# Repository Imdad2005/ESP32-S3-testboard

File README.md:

# ESP32-S3 Testboard

A custom ESP32-S3 test and development board designed in KiCad 9 for embedded systems and IoT prototyping.
Integrates the ESP32-S3-WROOM-1 module with power regulation, onboard sensing, programming interfaces,
and peripheral expansion on a compact 50 × 50 mm PCB.

---

## Board Preview

| Top | Bottom |
|-----|--------|
|  |  |

---

## Features

- **ESP32-S3-WROOM-1** — Wi-Fi + Bluetooth module, 8 MB flash
- **USB-C** — power and programming interface with ESD protection
- **Si7021-A20** — onboard temperature and humidity sensor
- **QWIIC connector** — I2C expansion for external sensors
- **BOOT / RESET / User buttons**
- **RGB LED** and 3.3 V power indicator LED
- **2×5 SPI expansion header**
- **2×3 programming header**
- **4× mounting holes** (3.2 mm)

---

## Power

| Rail  | Source                         |
|-------|--------------------------------|
| 5 V   | USB-C                          |
| 3.3 V | LM1117MP-3.3 voltage regulator |

---

## PCB Specifications

| Parameter        | Value      |
|------------------|------------|
| EDA Tool         | KiCad 9    |
| Copper Layers    | 4          |
| Board Dimensions | 50 × 50 mm |
| Mounting Holes   | 4 × 3.2 mm |

---

## Repository Structure

```
ESP32-S3-testboard/
├── hardware/
│   ├── ESP32-S3-testboard.kicad_pro
│   ├── ESP32-S3-testboard.kicad_sch
│   └── ESP32-S3-testboard.kicad_pcb
├── fabrications/
│   ├── BOM.csv
│   └── gerbers.zip
├── docs/
│   ├── ESP32-S3-testboard.pdf
│   ├── esp32-s3-wroom-2_datasheet_en.pdf
│   ├── pcb_top.png
│   └── pcb_bottom.png
├── .gitignore
└── README.md
```

---

## Tools

- [KiCad 9](https://www.kicad.org/)

---

## Author

**Imdad Aqueel**  
B.Tech in Electronic and Communication Engineering, Bengaluru

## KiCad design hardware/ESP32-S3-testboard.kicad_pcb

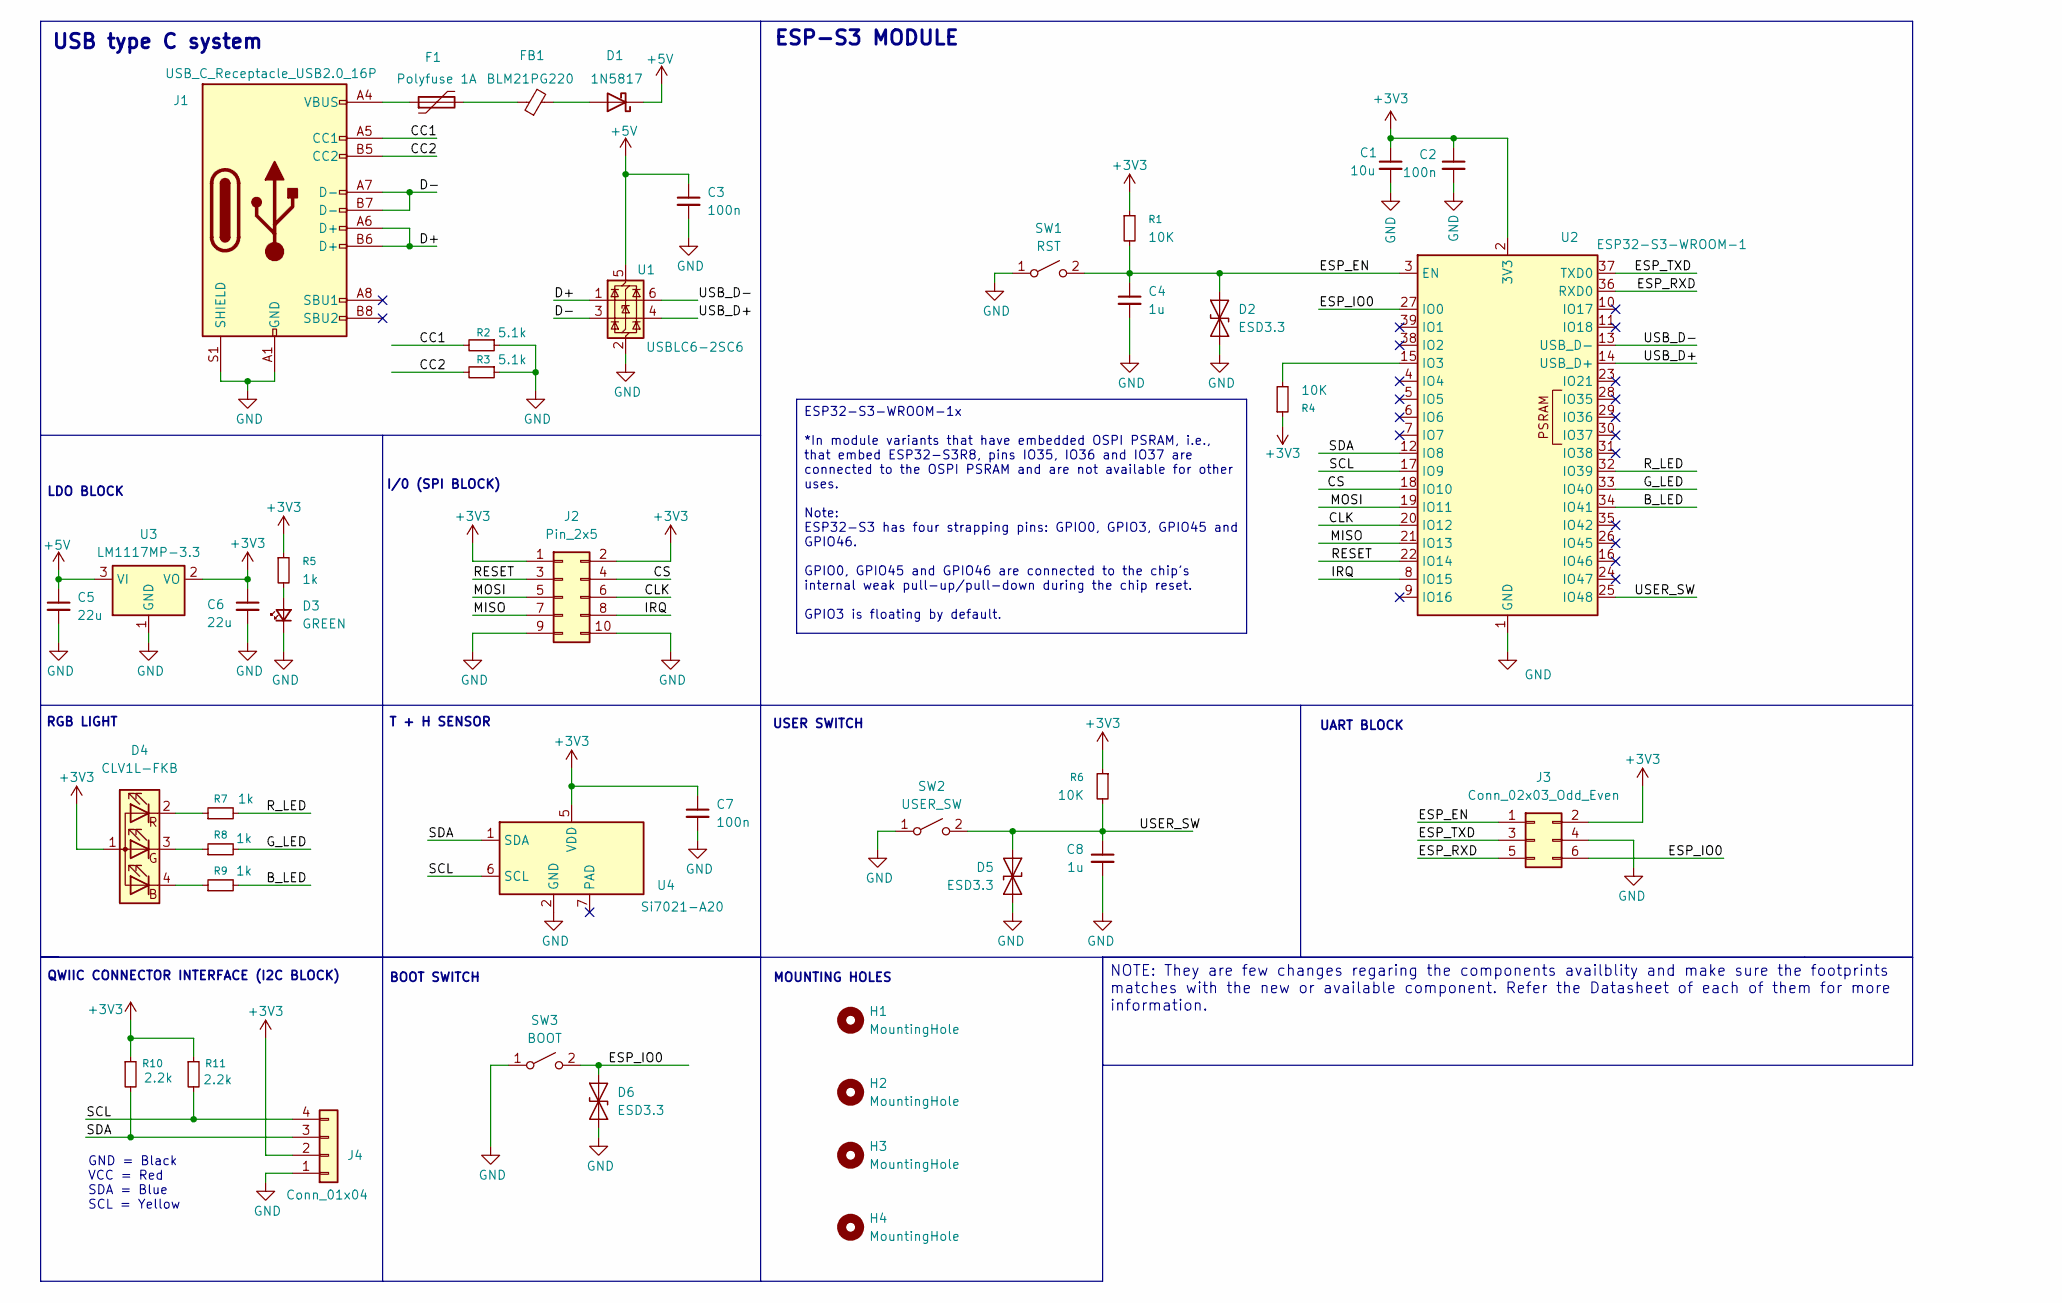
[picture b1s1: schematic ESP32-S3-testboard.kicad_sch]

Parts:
C1: 10u; C_0603_1608Metric
C2, C3, C7: 100n; C_0402_1005Metric_Pad0.74x0.62mm_HandSolder
C4, C8: 1u; C_0603_1608Metric
C5, C6: 22u; C_0805_2012Metric
D1: 1N5817; D_DO-41_SOD81_P10.16mm_Horizontal
D2, D5, D6: ESD3.3; D_SOD-923
D3: GREEN; LED_0603_1608Metric
D4: CLV1L-FKB; LED_Cree-PLCC4_3.2x2.8mm_CCW
F1: Polyfuse 1A; Fuse_1206_3216Metric
FB1: BLM21PG220; L_0805_2012Metric
H1, H2, H3, H4: MountingHole; MountingHole_3.2mm_M3
J1: USB_C_Receptacle_USB2.0_16P; USB_C_Receptacle_GCT_USB4105-xx-A_16P_TopMnt_Horizontal
J2: Pin_2x5; PinHeader_2x05_P2.54mm_Vertical
J3: Conn_02x03_Odd_Even; PinHeader_2x03_P2.54mm_Vertical
J4: Conn_01x04; JST_SH_SM04B-SRSS-TB_1x04-1MP_P1.00mm_Horizontal
R1, R4, R6: 10K; R_0402_1005Metric_Pad0.72x0.64mm_HandSolder
R2, R3: 5.1k; R_0402_1005Metric_Pad0.72x0.64mm_HandSolder
R5, R7, R8, R9: 1k; R_0402_1005Metric_Pad0.72x0.64mm_HandSolder
R10, R11: 2.2k; R_0402_1005Metric_Pad0.72x0.64mm_HandSolder
SW1: RST; SW_SPST_B3U-1000P
SW2: USER_SW; SW_Tactile_SPST_Angled_PTS645Vx31-2LFS
SW3: BOOT; SW_SPST_B3U-1000P
U1: USBLC6-2SC6; SOT-23-6
U2: ESP32-S3-WROOM-1
U3: LM1117MP-3.3; SOT-223-3_TabPin2
U4: Si7021-A20; DFN-6-1EP_3x3mm_P1mm_EP1.5x2.4mm

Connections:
+3V3: C1.1, C2.1, C6.1, C7.1, D4.1 (A), J2.1, J2.2, J3.2, J4.2, R1.1, R4.1, R5.1, R6.1, R10.1, R11.1, U2.2 (3V3), U3.2 (VO), U4.5 (VDD)
+5V: C3.1, C5.1, D1.1 (K), U1.5 (VBUS), U3.3 (VI)
/B_LED: R9.2, U2.34 (IO41)
/CC1: J1.A5 (CC1), R2.2
/CC2: J1.B5 (CC2), R3.2
/CLK: J2.6, U2.20 (IO12)
/CS: J2.4, U2.18 (IO10)
/D+: J1.A6 (D+), J1.B6 (D+), U1.1 (I/O1)
/D-: J1.A7 (D-), J1.B7 (D-), U1.3 (I/O2)
/ESP_EN: C4.1, D2.2 (A2), J3.1, R1.2, SW1.2 (B), U2.3 (EN)
/ESP_IO0: D6.2 (A2), J3.6, SW3.2 (B), U2.27 (IO0)
/ESP_RXD: J3.5, U2.36 (RXD0)
/ESP_TXD: J3.3, U2.37 (TXD0)
/G_LED: R8.2, U2.33 (IO40)
/IRQ: J2.8, U2.8 (IO15)
/MISO: J2.7, U2.21 (IO13)
/MOSI: J2.5, U2.19 (IO11)
/RESET: J2.3, U2.22 (IO14)
/R_LED: R7.2, U2.32 (IO39)
/SCL: J4.4, R11.2, U2.17 (IO9), U4.6 (SCL)
/SDA: J4.3, R10.2, U2.12 (IO8), U4.1 (SDA)
/USB_D+: U1.4 (I/O2), U2.14 (USB_D+)
/USB_D-: U1.6 (I/O1), U2.13 (USB_D-)
/USER_SW: C8.1, D5.2 (A2), R6.2, SW2.2 (B), U2.25 (IO48)
GND: C1.2, C2.2, C3.2, C4.2, C5.2, C6.2, C7.2, C8.2, D2.1 (A1), D3.1 (K), D5.1 (A1), D6.1 (A1), J1.A1 (GND), J1.A12 (GND), J1.B1 (GND), J1.B12 (GND), J1.S1 (SHIELD), J2.9, J2.10, J3.4, J4.1, R2.1, R3.1, SW1.1 (A), SW2.1 (A), SW3.1 (A), U1.2 (GND), U2.1 (GND), U2.40 (GND), U2.41 (GND), U3.1 (GND), U4.2 (GND)
unnamed: D1.2 (A), FB1.2
unnamed: D3.2 (A), R5.2
unnamed: D4.4 (BK), R9.1
unnamed: D4.3 (GK), R8.1
unnamed: D4.2 (RK), R7.1
unnamed: F1.1, J1.A4 (VBUS), J1.A9 (VBUS), J1.B4 (VBUS), J1.B9 (VBUS)
unnamed: F1.2, FB1.1
unnamed: R4.2, U2.15 (IO3)

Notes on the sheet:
LDO BLOCK
T + H SENSOR
UART BLOCK
BOOT SWITCH
USB type C system
ESP-S3 MODULE
I/0 (SPI BLOCK)
MOUNTING HOLES
GND = Black VCC = Red SDA = Blue SCL = Yellow
QWIIC CONNECTOR INTERFACE (I2C BLOCK)
RGB LIGHT
USER SWITCH
ESP32-S3-WROOM-1x *In module variants that have embedded OSPI PSRAM, i.e., that embed ESP32-S3R8, pins IO35, IO36 and IO37 are connected to the OSPI PSRAM and are not available for other uses. Note: ESP32-S3 has four strapping pins: GPIO0, GPIO3, GPIO45 and GPIO46. GPIO0, GPIO45 and GPIO46 are conn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
NOTE: They are few changes regaring the components availblity and make sure the footprints matches with the new or available component. Refer the Datasheet of each of them for more information.

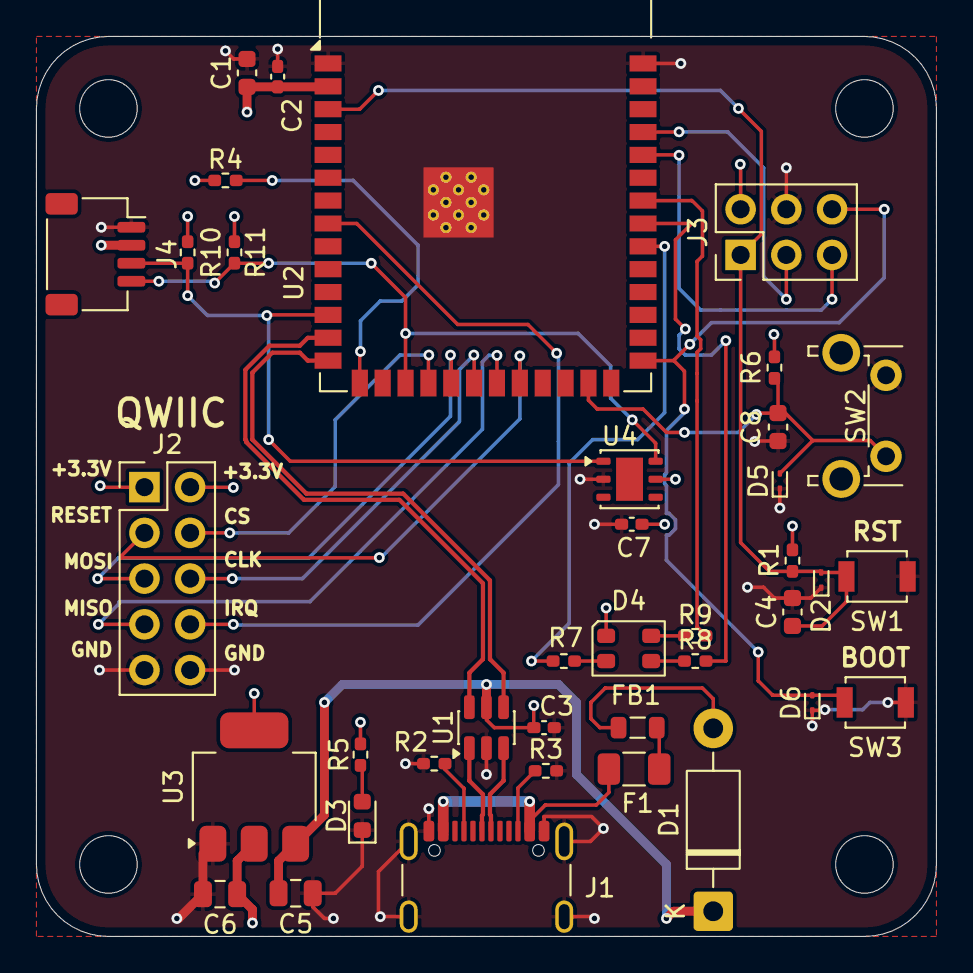
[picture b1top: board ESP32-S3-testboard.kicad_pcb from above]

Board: 4 copper layers, 50.0 x 50.0 mm, 42 parts (0 on the bottom side), 33 nets.

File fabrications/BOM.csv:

"Reference","Qty","Value","DNP","Exclude from BOM","Exclude from Board","Footprint"
"C1","1","10u","","","","Capacitor_SMD:C_0603_1608Metric"
"C2,C3,C7","3","100n","","","","Capacitor_SMD:C_0402_1005Metric_Pad0.74x0.62mm_HandSolder"
"C4,C8","2","1u","","","","Capacitor_SMD:C_0603_1608Metric"
"C5,C6","2","22u","","","","Capacitor_SMD:C_0805_2012Metric"
"D1","1","1N5817","","","","Diode_THT:D_DO-41_SOD81_P10.16mm_Horizontal"
"D2,D5,D6","3","ESD3.3","","","","Diode_SMD:D_SOD-923"
"D3","1","GREEN","","","","LED_SMD:LED_0603_1608Metric"
"D4","1","CLV1L-FKB","","","","LED_SMD:LED_Cree-PLCC4_3.2x2.8mm_CCW"
"F1","1","Polyfuse 1A","","","","Fuse:Fuse_1206_3216Metric"
"FB1","1","BLM21PG220","","","","Inductor_SMD:L_0805_2012Metric"
"H1,H2,H3,H4","4","MountingHole","","Excluded from BOM","","MountingHole:MountingHole_3.2mm_M3"
"J1","1","USB_C_Receptacle_USB2.0_16P","","","","Connector_USB:USB_C_Receptacle_GCT_USB4105-xx-A_16P_TopMnt_Horizontal"
"J2","1","Pin_2x5","","","","Connector_PinHeader_2.54mm:PinHeader_2x05_P2.54mm_Vertical"
"J3","1","Conn_02x03_Odd_Even","","","","Connector_PinHeader_2.54mm:PinHeader_2x03_P2.54mm_Vertical"
"J4","1","Conn_01x04","","","","Connector_JST:JST_SH_SM04B-SRSS-TB_1x04-1MP_P1.00mm_Horizontal"
"R1,R4,R6","3","10K","","","","Resistor_SMD:R_0402_1005Metric_Pad0.72x0.64mm_HandSolder"
"R2,R3","2","5.1k","","","","Resistor_SMD:R_0402_1005Metric_Pad0.72x0.64mm_HandSolder"
"R5,R7,R8,R9","4","1k","","","","Resistor_SMD:R_0402_1005Metric_Pad0.72x0.64mm_HandSolder"
"R10,R11","2","2.2k","","","","Resistor_SMD:R_0402_1005Metric_Pad0.72x0.64mm_HandSolder"
"SW1","1","RST","","","","Button_Switch_SMD:SW_SPST_B3U-1000P"
"SW2","1","USER_SW","","","","Button_Switch_THT:SW_Tactile_SPST_Angled_PTS645Vx31-2LFS"
"SW3","1","BOOT","","","","Button_Switch_SMD:SW_SPST_B3U-1000P"
"U1","1","USBLC6-2SC6","","","","Package_TO_SOT_SMD:SOT-23-6"
"U2","1","ESP32-S3-WROOM-1","","","","RF_Module:ESP32-S3-WROOM-1"
"U3","1","LM1117MP-3.3","","","","Package_TO_SOT_SMD:SOT-223-3_TabPin2"
"U4","1","Si7021-A20","","","","Package_DFN_QFN:DFN-6-1EP_3x3mm_P1mm_EP1.5x2.4mm"
